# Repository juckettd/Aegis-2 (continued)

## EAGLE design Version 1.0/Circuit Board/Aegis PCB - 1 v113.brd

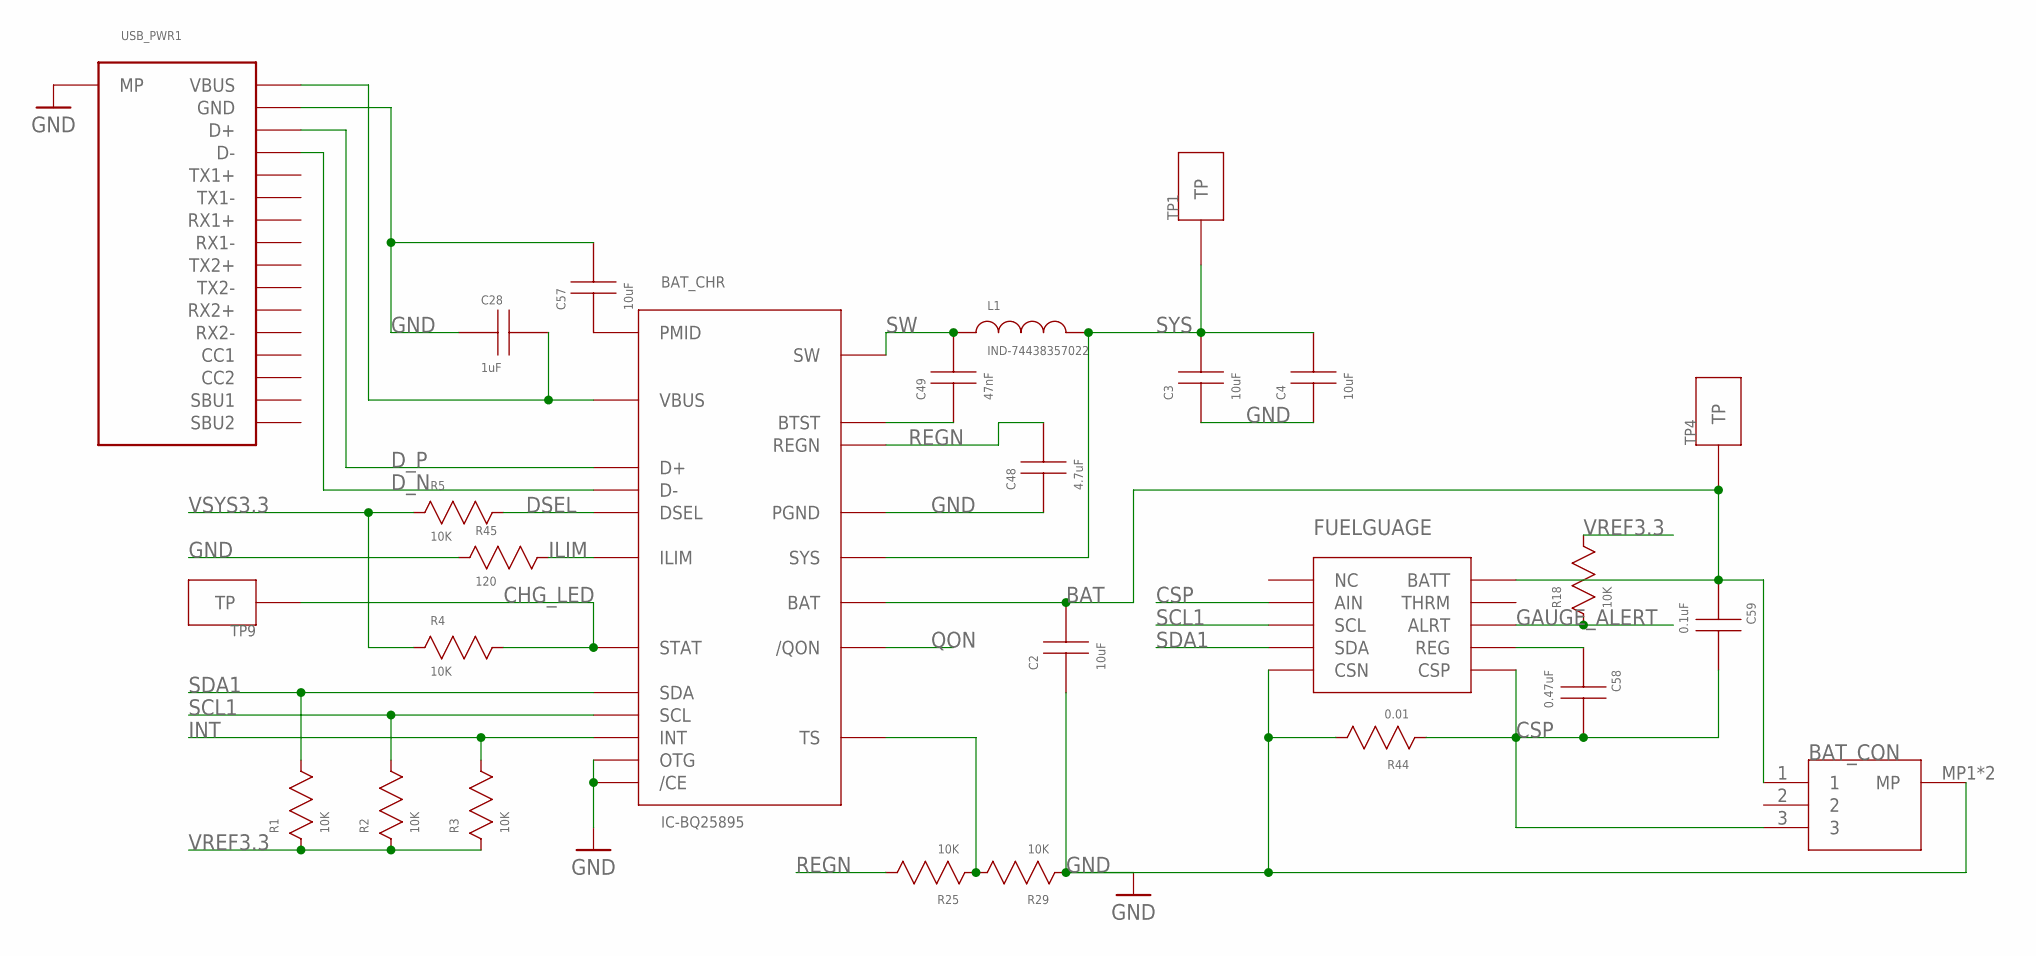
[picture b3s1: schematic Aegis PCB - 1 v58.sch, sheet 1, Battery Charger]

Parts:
BAT_CHR: IC-BQ25895
BAT_CON: CONN-AUH03; CONN_AUH03
C2, C3, C4, C57: 10uF; CAP-603
C28: 1uF; CAP-603
C48: 4.7uF; CAP-603
C49: 47nF; CAP-603
C58: 0.47uF; CAP-603
C59: 0.1uF; CAP-603
FUELGUAGE: IC-MAX17055
L1: IND-74438357022
R1, R2, R3, R4, R5, R18, R25, R29: 10K; RES-603
R44: 0.01; RES-603
R45: 120; RES-603
TP1, TP4, TP9: TESTPOINT
USB_PWR1: USBC-USB-C31-S-RA-CS1D-BK-T/R

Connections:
BAT: BAT_CHR.BAT1 (BAT), BAT_CHR.BAT2 (BAT), BAT_CON.1, C2.C, C59.A, FUELGUAGE.BATT, TP4.TP
CHG_LED: BAT_CHR.STAT, R4.C, TP9.TP; also elsewhere on the board
CSP: BAT_CON.3, C58.C, C59.C, FUELGUAGE.AIN, FUELGUAGE.CSP, FUELGUAGE.EP (CSP), R44.A
DSEL: BAT_CHR.DSEL, R5.C
D_N: BAT_CHR.D-, USB_PWR1.D-, USB_PWR1.D-_2 (D-)
D_P: BAT_CHR.D+, USB_PWR1.D+, USB_PWR1.D+_2 (D+)
GAUGE_ALERT: FUELGUAGE.ALRT, R18.A; also elsewhere on the board
ILIM: BAT_CHR.ILIM, R45.C
INT: BAT_CHR.INT, R3.C; also elsewhere on the board
unnamed: BAT_CHR.BTST, C49.A
unnamed: BAT_CHR.VBUS, C28.C, USB_PWR1.VBUS_1 (VBUS), USB_PWR1.VBUS_2 (VBUS), USB_PWR1.VBUS_3 (VBUS), USB_PWR1.VBUS_4 (VBUS)
unnamed: BAT_CHR.TS, R25.A, R29.C
unnamed: BAT_CHR.PMID, C57.A
unnamed: C58.A, FUELGUAGE.REG
QON: BAT_CHR./QON
REGN: BAT_CHR.REGN, C48.C, R25.C
SCL1: BAT_CHR.SCL, FUELGUAGE.SCL, R2.C; also elsewhere on the board
SDA1: BAT_CHR.SDA, FUELGUAGE.SDA, R1.C; also elsewhere on the board
SW: BAT_CHR.SW1 (SW), BAT_CHR.SW2 (SW), C49.C, L1.A
SYS: BAT_CHR.SYS1 (SYS), BAT_CHR.SYS2 (SYS), C3.C, C4.C, L1.C, TP1.TP; also elsewhere on the board
VREF3.3: R1.A, R2.A, R3.A, R18.C; also elsewhere on the board
VSYS3.3: R4.A, R5.A; also elsewhere on the board

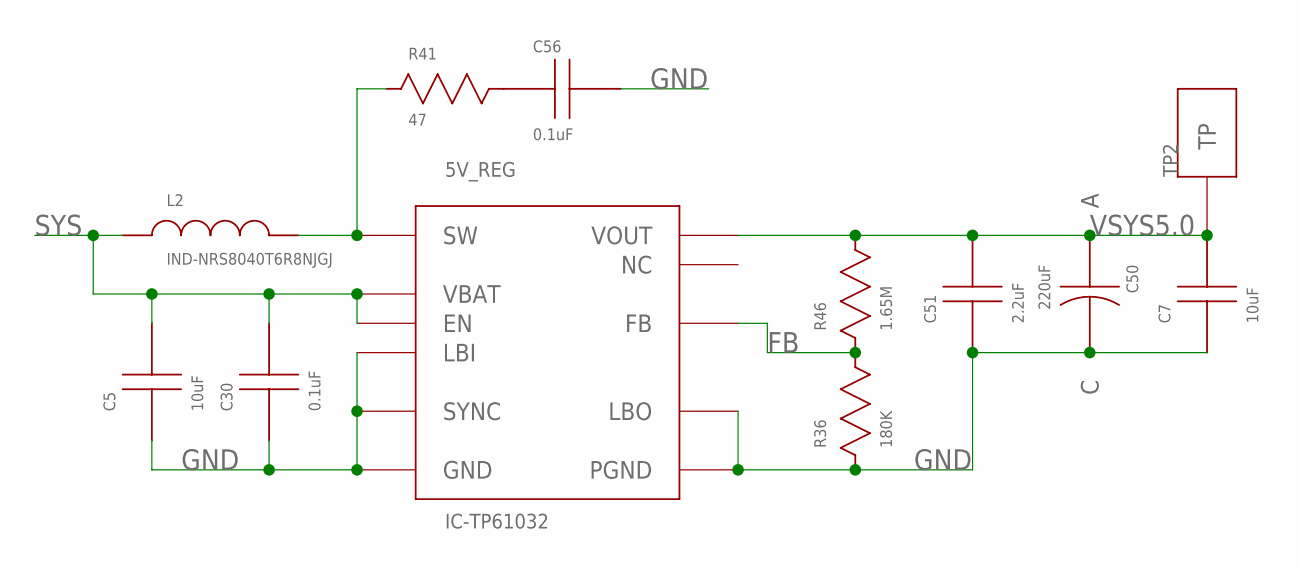
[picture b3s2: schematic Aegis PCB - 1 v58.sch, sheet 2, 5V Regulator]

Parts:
5V_REG: IC-TP61032; IC-TPS61032
C5, C7: 10uF; CAP-603
C30, C56: 0.1uF; CAP-603
C50: 220uF; CAP-TAN-1411
C51: 2.2uF; CAP-603
L2: IND-NRS8040T6R8NJGJ
R36: 180K; RES-603
R41: 47; RES-603
R46: 1.65M; RES-603
TP2: TESTPOINT

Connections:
FB: 5V_REG.FB, R36.C, R46.A
unnamed: C56.A, R41.C
SNUB: 5V_REG.SW1 (SW), 5V_REG.SW2 (SW), L2.C, R41.A
SYS: 5V_REG.EN, 5V_REG.VBAT, C5.C, C30.C, L2.A; also elsewhere on the board
VSYS5.0: 5V_REG.VOUT1 (VOUT), 5V_REG.VOUT2 (VOUT), 5V_REG.VOUT3 (VOUT), C7.C, C50.A, C51.C, R46.C, TP2.TP; also elsewhere on the board

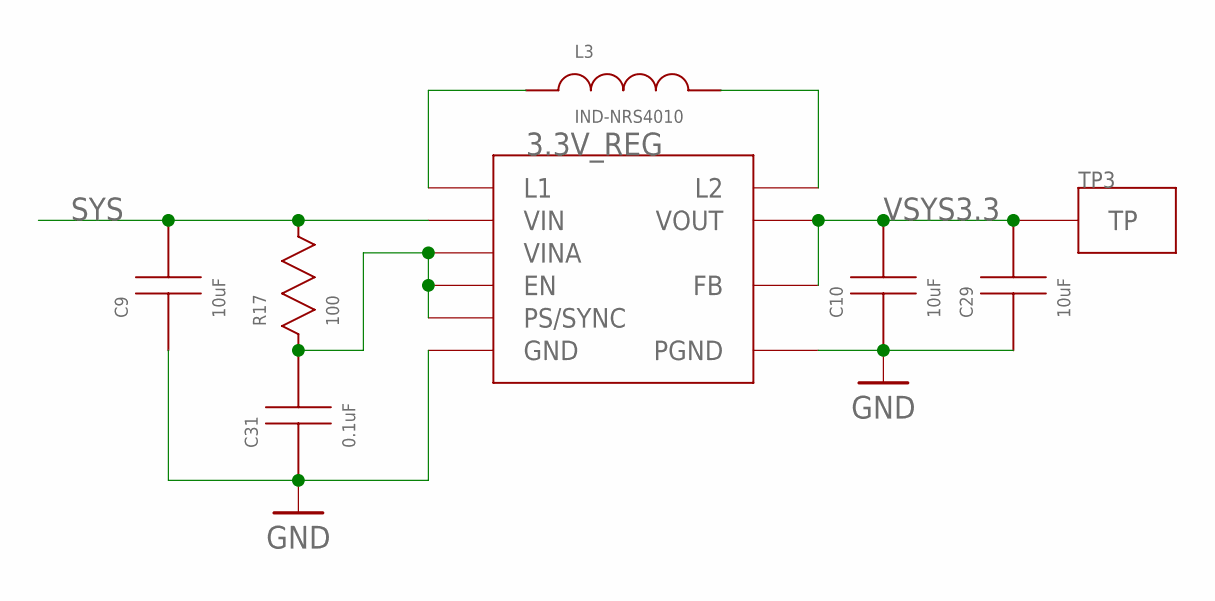
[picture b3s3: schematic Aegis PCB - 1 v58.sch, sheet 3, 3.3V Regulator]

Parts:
3.3V_REG: IC-TPS63001DRCR
C9, C10, C29: 10uF; CAP-603
C31: 0.1uF; CAP-603
L3: IND-NRS4010
R17: 100; RES-603
TP3: TESTPOINT

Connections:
unnamed: 3.3V_REG.EN, 3.3V_REG.PS/SYNC, 3.3V_REG.VINA, C31.C, R17.A
unnamed: 3.3V_REG.L1, L3.A
unnamed: 3.3V_REG.L2, L3.C
SYS: 3.3V_REG.VIN, C9.C, R17.C; also elsewhere on the board
VSYS3.3: 3.3V_REG.FB, 3.3V_REG.VOUT, C10.C, C29.C, TP3.TP; also elsewhere on the board

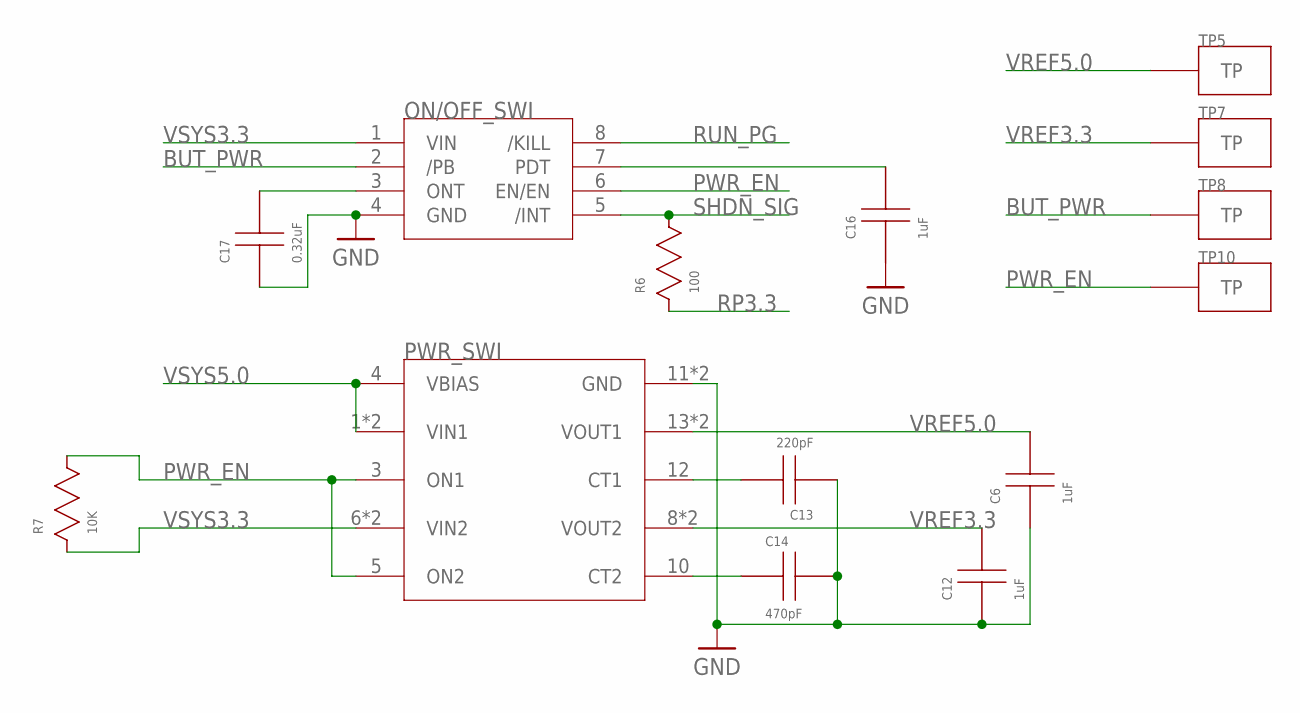
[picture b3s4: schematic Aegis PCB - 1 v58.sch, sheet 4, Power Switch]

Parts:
C6, C12, C16: 1uF; CAP-603
C13: 220pF; CAP-603
C14: 470pF; CAP-603
C17: 0.32uF; CAP-603
ON/OFF_SWI: IC-LTC2954
PWR_SWI: IC-TPS22976
R6: 100; RES-603
R7: 10K; RES-603
TP5, TP7, TP8, TP10: TESTPOINT

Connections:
BUT_PWR: ON/OFF_SWI.2 (/PB), TP8.TP; also elsewhere on the board
unnamed: C13.C, PWR_SWI.12 (CT1)
unnamed: C14.A, PWR_SWI.10 (CT2)
unnamed: C16.C, ON/OFF_SWI.7 (PDT)
unnamed: C17.C, ON/OFF_SWI.3 (ONT)
PWR_EN: ON/OFF_SWI.6 (EN/EN), PWR_SWI.3 (ON1), PWR_SWI.5 (ON2), R7.C, TP10.TP
RP3.3: R6.A; also elsewhere on the board
RUN_PG: ON/OFF_SWI.8 (/KILL); also elsewhere on the board
SHDN_SIG: ON/OFF_SWI.5 (/INT), R6.C; also elsewhere on the board
VREF3.3: C12.C, PWR_SWI.8 (VOUT2), PWR_SWI.9 (VOUT2), TP7.TP; also elsewhere on the board
VREF5.0: C6.C, PWR_SWI.13 (VOUT1), PWR_SWI.14 (VOUT1), TP5.TP; also elsewhere on the board
VSYS3.3: ON/OFF_SWI.1 (VIN), PWR_SWI.6 (VIN2), PWR_SWI.7 (VIN2), R7.A; also elsewhere on the board
VSYS5.0: PWR_SWI.1 (VIN1), PWR_SWI.2 (VIN1), PWR_SWI.4 (VBIAS); also elsewhere on the board

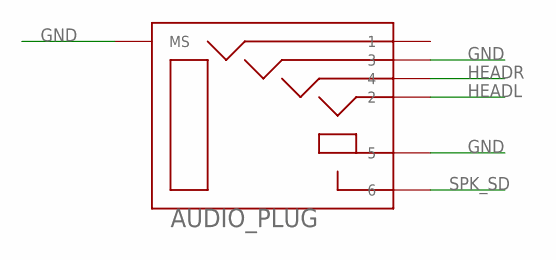
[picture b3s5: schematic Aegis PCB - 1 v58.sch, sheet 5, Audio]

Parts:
AUDIO_PLUG: AUDIOPLUG-ASJ-192-Y-TR

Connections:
HEADL: AUDIO_PLUG.2; also elsewhere on the board
HEADR: AUDIO_PLUG.4; also elsewhere on the board
SPK_SD: AUDIO_PLUG.6; also elsewhere on the board

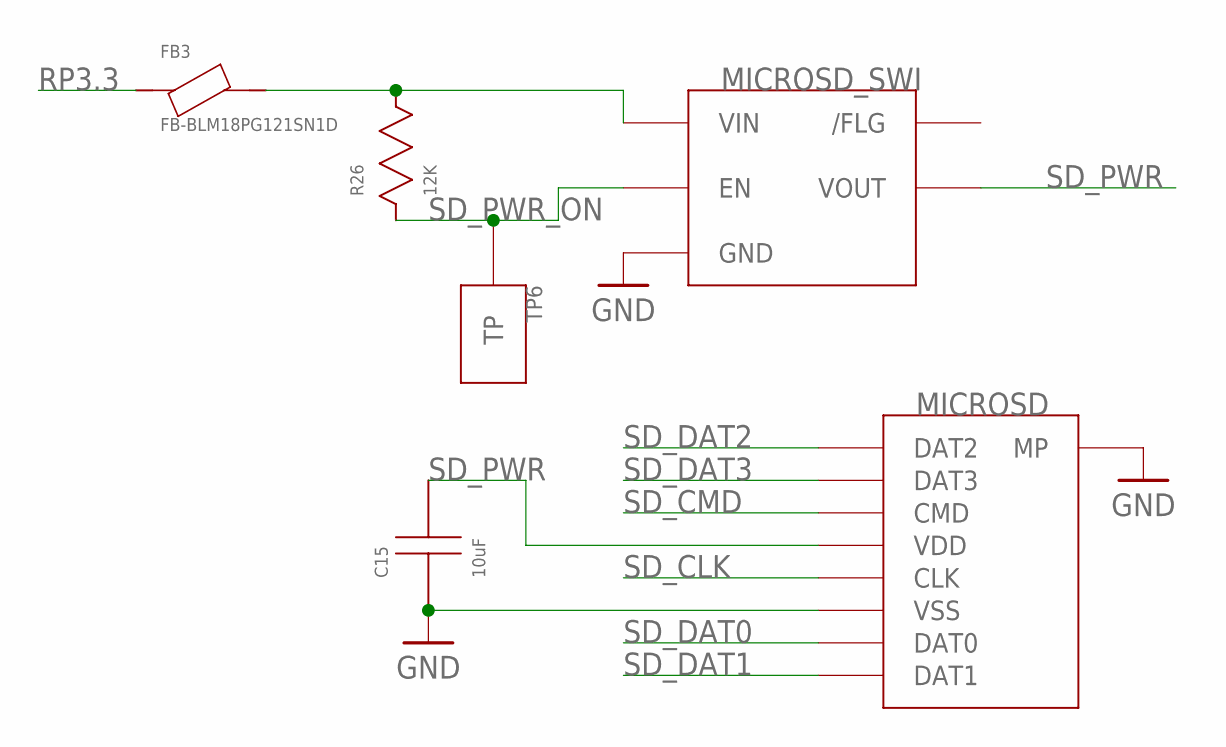
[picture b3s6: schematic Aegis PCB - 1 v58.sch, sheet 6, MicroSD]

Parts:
C15: 10uF; CAP-603
FB3: FB-BLM18PG121SN1D
MICROSD: MICROSD-5033981892_SD
MICROSD_SWI: IC-RT9742
R26: 12K; RES-603
TP6: TESTPOINT

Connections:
unnamed: FB3.C, MICROSD_SWI.VIN, R26.C
RP3.3: FB3.A; also elsewhere on the board
SD_CLK: MICROSD.CLK; also elsewhere on the board
SD_CMD: MICROSD.CMD; also elsewhere on the board
SD_DAT0: MICROSD.DAT0; also elsewhere on the board
SD_DAT1: MICROSD.DAT1; also elsewhere on the board
SD_DAT2: MICROSD.DAT2; also elsewhere on the board
SD_DAT3: MICROSD.DAT3; also elsewhere on the board
SD_PWR: C15.C, MICROSD.VDD, MICROSD_SWI.VOUT
SD_PWR_ON: MICROSD_SWI.EN, R26.A, TP6.TP; also elsewhere on the board

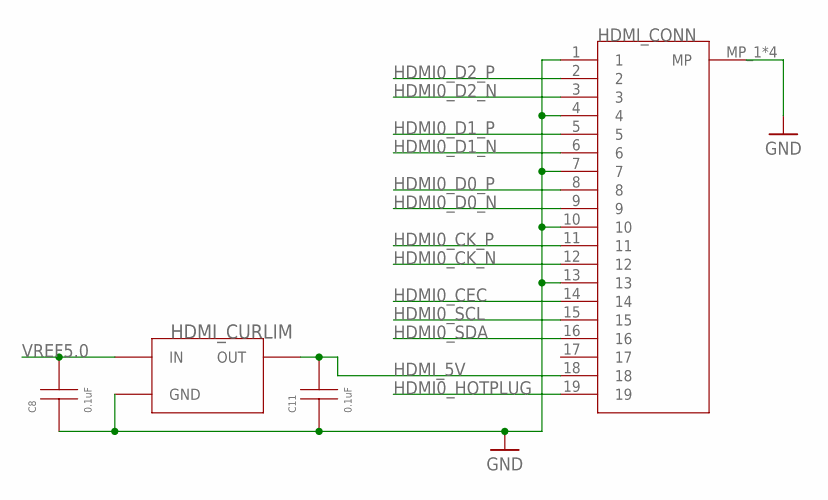
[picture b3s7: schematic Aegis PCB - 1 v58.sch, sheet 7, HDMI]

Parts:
C8, C11: 0.1uF; CAP-603
HDMI_CONN: HDMI-2001-1-2-21-00-BK
HDMI_CURLIM: CURLIM-AP2331

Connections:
HDMI0_CEC: HDMI_CONN.14; also elsewhere on the board
HDMI0_CK_N: HDMI_CONN.12; also elsewhere on the board
HDMI0_CK_P: HDMI_CONN.11; also elsewhere on the board
HDMI0_D0_N: HDMI_CONN.9; also elsewhere on the board
HDMI0_D0_P: HDMI_CONN.8; also elsewhere on the board
HDMI0_D1_N: HDMI_CONN.6; also elsewhere on the board
HDMI0_D1_P: HDMI_CONN.5; also elsewhere on the board
HDMI0_D2_N: HDMI_CONN.3; also elsewhere on the board
HDMI0_D2_P: HDMI_CONN.2; also elsewhere on the board
HDMI0_HOTPLUG: HDMI_CONN.19; also elsewhere on the board
HDMI0_SCL: HDMI_CONN.15; also elsewhere on the board
HDMI0_SDA: HDMI_CONN.16; also elsewhere on the board
HDMI_5V: C11.C, HDMI_CONN.18, HDMI_CURLIM.OUT
VREF5.0: C8.C, HDMI_CURLIM.IN; also elsewhere on the board

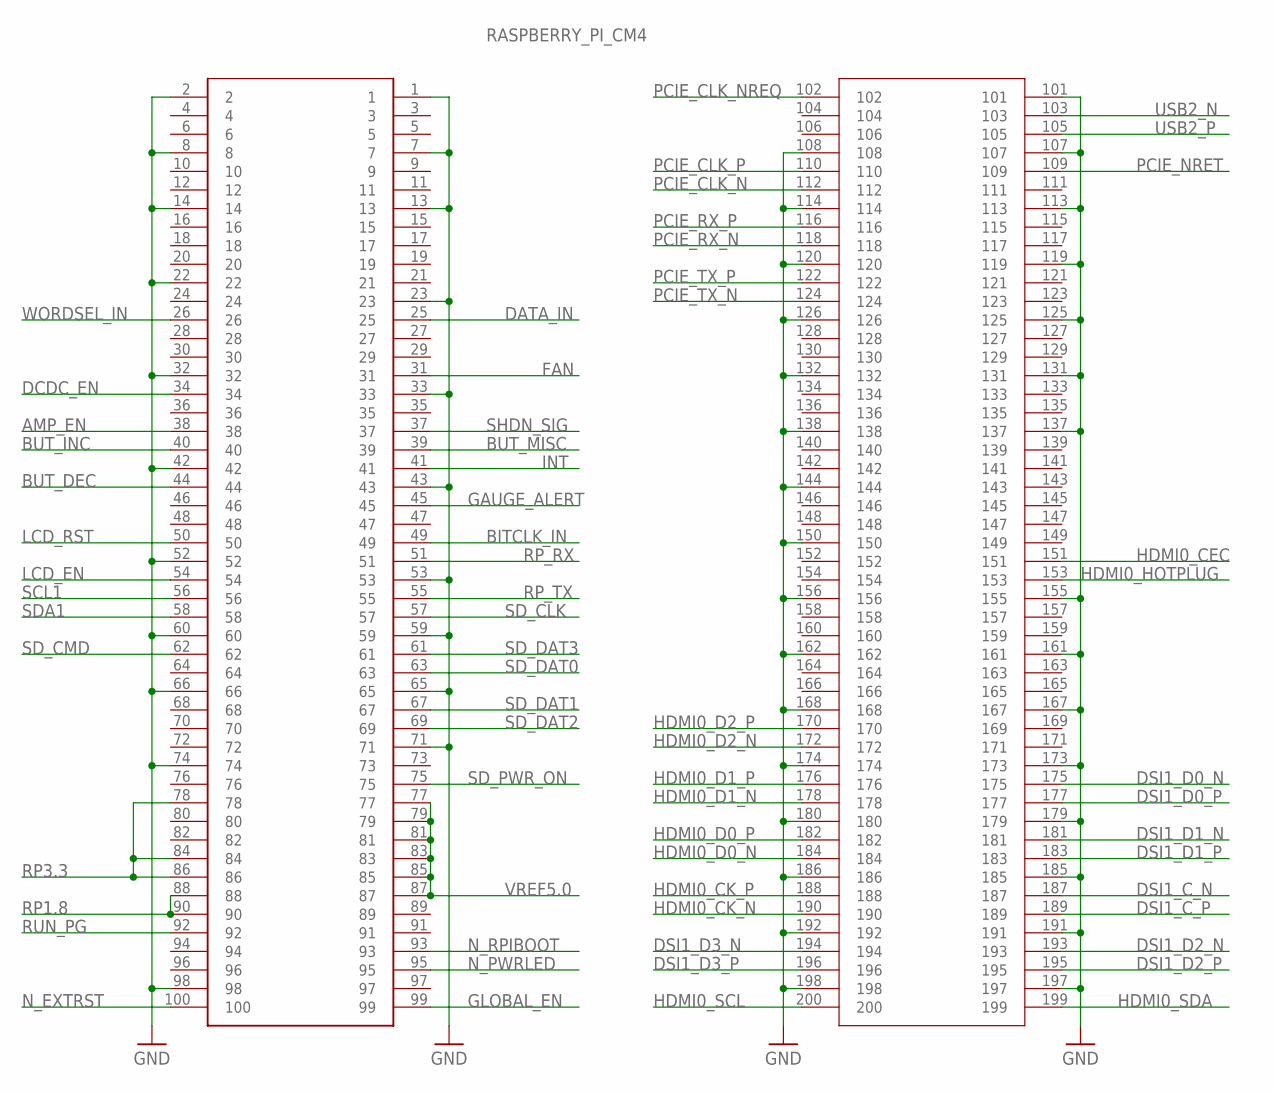
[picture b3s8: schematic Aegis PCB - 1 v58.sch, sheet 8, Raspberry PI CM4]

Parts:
RASPBERRY_PI_CM4: RP_CM4

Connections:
AMP_EN: RASPBERRY_PI_CM4.38; also elsewhere on the board
BITCLK_IN: RASPBERRY_PI_CM4.49; also elsewhere on the board
BUT_DEC: RASPBERRY_PI_CM4.44; also elsewhere on the board
BUT_INC: RASPBERRY_PI_CM4.40; also elsewhere on the board
BUT_MISC: RASPBERRY_PI_CM4.39; also elsewhere on the board
DATA_IN: RASPBERRY_PI_CM4.25; also elsewhere on the board
DCDC_EN: RASPBERRY_PI_CM4.34; also elsewhere on the board
DSI1_C_N: RASPBERRY_PI_CM4.187; also elsewhere on the board
DSI1_C_P: RASPBERRY_PI_CM4.189; also elsewhere on the board
DSI1_D0_N: RASPBERRY_PI_CM4.175; also elsewhere on the board
DSI1_D0_P: RASPBERRY_PI_CM4.177; also elsewhere on the board
DSI1_D1_N: RASPBERRY_PI_CM4.181; also elsewhere on the board
DSI1_D1_P: RASPBERRY_PI_CM4.183; also elsewhere on the board
DSI1_D2_N: RASPBERRY_PI_CM4.193; also elsewhere on the board
DSI1_D2_P: RASPBERRY_PI_CM4.195; also elsewhere on the board
DSI1_D3_N: RASPBERRY_PI_CM4.194; also elsewhere on the board
DSI1_D3_P: RASPBERRY_PI_CM4.196; also elsewhere on the board
FAN: RASPBERRY_PI_CM4.31; also elsewhere on the board
GAUGE_ALERT: RASPBERRY_PI_CM4.45; also elsewhere on the board
GLOBAL_EN: RASPBERRY_PI_CM4.99
HDMI0_CEC: RASPBERRY_PI_CM4.151; also elsewhere on the board
HDMI0_CK_N: RASPBERRY_PI_CM4.190; also elsewhere on the board
HDMI0_CK_P: RASPBERRY_PI_CM4.188; also elsewhere on the board
HDMI0_D0_N: RASPBERRY_PI_CM4.184; also elsewhere on the board
HDMI0_D0_P: RASPBERRY_PI_CM4.182; also elsewhere on the board
HDMI0_D1_N: RASPBERRY_PI_CM4.178; also elsewhere on the board
HDMI0_D1_P: RASPBERRY_PI_CM4.176; also elsewhere on the board
HDMI0_D2_N: RASPBERRY_PI_CM4.172; also elsewhere on the board
HDMI0_D2_P: RASPBERRY_PI_CM4.170; also elsewhere on the board
HDMI0_HOTPLUG: RASPBERRY_PI_CM4.153; also elsewhere on the board
HDMI0_SCL: RASPBERRY_PI_CM4.200; also elsewhere on the board
HDMI0_SDA: RASPBERRY_PI_CM4.199; also elsewhere on the board
INT: RASPBERRY_PI_CM4.41; also elsewhere on the board
LCD_EN: RASPBERRY_PI_CM4.54; also elsewhere on the board
LCD_RST: RASPBERRY_PI_CM4.50; also elsewhere on the board
N_EXTRST: RASPBERRY_PI_CM4.100; also elsewhere on the board
N_PWRLED: RASPBERRY_PI_CM4.95; also elsewhere on the board
N_RPIBOOT: RASPBERRY_PI_CM4.93
PCIE_CLK_N: RASPBERRY_PI_CM4.112
PCIE_CLK_NREQ: RASPBERRY_PI_CM4.102
PCIE_CLK_P: RASPBERRY_PI_CM4.110
PCIE_NRET: RASPBERRY_PI_CM4.109
PCIE_RX_N: RASPBERRY_PI_CM4.118
PCIE_RX_P: RASPBERRY_PI_CM4.116
PCIE_TX_N: RASPBERRY_PI_CM4.124
PCIE_TX_P: RASPBERRY_PI_CM4.122
RP1.8: RASPBERRY_PI_CM4.88, RASPBERRY_PI_CM4.90; also elsewhere on the board
RP3.3: RASPBERRY_PI_CM4.78, RASPBERRY_PI_CM4.84, RASPBERRY_PI_CM4.86; also elsewhere on the board
RUN_PG: RASPBERRY_PI_CM4.92; also elsewhere on the board
SCL1: RASPBERRY_PI_CM4.56; also elsewhere on the board
SDA1: RASPBERRY_PI_CM4.58; also elsewhere on the board
SD_CLK: RASPBERRY_PI_CM4.57; also elsewhere on the board
SD_CMD: RASPBERRY_PI_CM4.62; also elsewhere on the board
SD_DAT0: RASPBERRY_PI_CM4.63; also elsewhere on the board
SD_DAT1: RASPBERRY_PI_CM4.67; also elsewhere on the board
SD_DAT2: RASPBERRY_PI_CM4.69; also elsewhere on the board
SD_DAT3: RASPBERRY_PI_CM4.61; also elsewhere on the board
SD_PWR_ON: RASPBERRY_PI_CM4.75; also elsewhere on the board
SHDN_SIG: RASPBERRY_PI_CM4.37; also elsewhere on the board
USB2_N: RASPBERRY_PI_CM4.103; also elsewhere on the board
USB2_P: RASPBERRY_PI_CM4.105; also elsewhere on the board
VREF5.0: RASPBERRY_PI_CM4.77, RASPBERRY_PI_CM4.79, RASPBERRY_PI_CM4.81, RASPBERRY_PI_CM4.83, RASPBERRY_PI_CM4.85, RASPBERRY_PI_CM4.87; also elsewhere on the board
WORDSEL_IN: RASPBERRY_PI_CM4.26; also elsewhere on the board

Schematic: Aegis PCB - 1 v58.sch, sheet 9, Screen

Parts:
FPC_SCREEN: CONN-FH35C-31S-0.3SHW
SD1: SCHDIODE-SN74LVC1G17
TP11, TP12, TP13, TP15: TESTPOINT

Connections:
DCDC_EN: FPC_SCREEN.30, TP11.TP; also elsewhere on the board
DSI1_C_N: FPC_SCREEN.15; also elsewhere on the board
DSI1_C_P: FPC_SCREEN.16; also elsewhere on the board
DSI1_D0_N: FPC_SCREEN.12; also elsewhere on the board
DSI1_D0_P: FPC_SCREEN.13; also elsewhere on the board
DSI1_D1_N: FPC_SCREEN.18; also elsewhere on the board
DSI1_D1_P: FPC_SCREEN.19; also elsewhere on the board
DSI1_D2_N: FPC_SCREEN.21; also elsewhere on the board
DSI1_D2_P: FPC_SCREEN.22; also elsewhere on the board
DSI1_D3_N: FPC_SCREEN.9; also elsewhere on the board
DSI1_D3_P: FPC_SCREEN.10; also elsewhere on the board
LCD_EN: FPC_SCREEN.6, TP15.TP; also elsewhere on the board
LCD_RST: SD1.2 (A), TP13.TP; also elsewhere on the board
LCD_RST_ADJ: FPC_SCREEN.24, SD1.4 (Y), TP12.TP; also elsewhere on the board
RP1.8: FPC_SCREEN.31, SD1.5 (VCC); also elsewhere on the board
RP3.3: FPC_SCREEN.26, FPC_SCREEN.27; also elsewhere on the board
VREF3.3: FPC_SCREEN.1, FPC_SCREEN.2, FPC_SCREEN.3, FPC_SCREEN.4; also elsewhere on the board

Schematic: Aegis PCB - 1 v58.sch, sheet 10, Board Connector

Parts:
BOARD_CONN1: CONN-AXK5F30347YG

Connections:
AMP_EN: BOARD_CONN1.10; also elsewhere on the board
BITCLK_IN: BOARD_CONN1.2; also elsewhere on the board
BUT_DEC: BOARD_CONN1.5; also elsewhere on the board
BUT_INC: BOARD_CONN1.6; also elsewhere on the board
BUT_MISC: BOARD_CONN1.7; also elsewhere on the board
BUT_PWR: BOARD_CONN1.8; also elsewhere on the board
CHG_LED: BOARD_CONN1.9; also elsewhere on the board
DATA_IN: BOARD_CONN1.4; also elsewhere on the board
HEADL: BOARD_CONN1.12; also elsewhere on the board
HEADR: BOARD_CONN1.13; also elsewhere on the board
N_PWRLED: BOARD_CONN1.1; also elsewhere on the board
SPK_SD: BOARD_CONN1.11; also elsewhere on the board
TD_N: BOARD_CONN1.15; also elsewhere on the board
TD_P: BOARD_CONN1.14; also elsewhere on the board
VREF3.3: BOARD_CONN1.26, BOARD_CONN1.27, BOARD_CONN1.28, BOARD_CONN1.29; also elsewhere on the board
VSYS3.3: BOARD_CONN1.30; also elsewhere on the board
WORDSEL_IN: BOARD_CONN1.3; also elsewhere on the board

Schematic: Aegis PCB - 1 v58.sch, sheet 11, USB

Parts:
C1: 100uF; CAP-603
C19, C20, C21: 10uF; CAP-603
C43: 0.1uF; CAP-603
C52, C53: 27pF; CAP-603
CLK_24M: CLK-ECS-240
R27: 12K; RES-603
R28: 15K; RES-603
R30, R31, R32, R33: 36K; RES-603
TP14: TESTPOINT
USB_CURLIM: CURLIM-AP22653W6
USB_HUB: USBPORT-USB2514BT-I/M2
USB_POE: POE_PROT-TPD4EUSB30DQAR
USB_PWR2: USBC-USB-C31-S-RA-CS1D-BK-T/R

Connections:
D1_N: USB_HUB.3, USB_POE.D1-, USB_PWR2.D-, USB_PWR2.D-_2 (D-)
D1_P: USB_HUB.4, USB_POE.D1+, USB_PWR2.D+, USB_PWR2.D+_2 (D+)
unnamed: R32.A, USB_HUB.28
unnamed: R28.C, USB_CURLIM.ILIM
unnamed: R31.A, USB_HUB.22
unnamed: R30.A, USB_HUB.24
unnamed: C53.C, CLK_24M.OUT/IN, USB_HUB.32
unnamed: C52.C, CLK_24M.IN/OUT, USB_HUB.33
unnamed: R33.A, USB_HUB.25
unnamed: R27.A, USB_HUB.35
N_EXTRST: USB_HUB.26; also elsewhere on the board
N_OCS1: USB_CURLIM.NFAULT, USB_HUB.13, USB_HUB.17, USB_HUB.19, USB_HUB.21
PWR1: USB_CURLIM.EN, USB_HUB.12
TD_N: USB_HUB.1, USB_POE.D2-; also elsewhere on the board
TD_P: USB_HUB.2, USB_POE.D2+; also elsewhere on the board
USB2_N: USB_HUB.30; also elsewhere on the board
USB2_P: USB_HUB.31; also elsewhere on the board
VREF3.3: C19.C, C43.C, USB_HUB.5, USB_HUB.10, USB_HUB.15, USB_HUB.23, USB_HUB.27, USB_HUB.29, USB_HUB.36; also elsewhere on the board
VREF5.0: C20.C, USB_CURLIM.IN; also elsewhere on the board

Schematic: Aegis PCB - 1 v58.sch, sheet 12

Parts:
C44: 0.1uF; CAP-603
D3: DIODE-X3-WLB1608-2
FAN_CONN: CONN-282834-2
R19: 10K; RES-603
TP16: TESTPOINT
TR3: TRAN-DMG2302UKQ

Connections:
FAN: R19.C, TP16.TP, TR3.G; also elsewhere on the board
unnamed: D3.A, FAN_CONN.2, TR3.D
VREF3.3: C44.C, D3.C, FAN_CONN.1; also elsewhere on the board

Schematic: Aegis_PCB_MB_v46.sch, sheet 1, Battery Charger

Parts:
BAT_CHR: IC-BQ25895
BAT_CON: CONN-AUH03; CONN_AUH03
C2, C3, C4, C57: 10uF; CAP-603
C28: 1uF; CAP-603
C48: 4.7uF; CAP-603
C49: 47nF; CAP-603
C58: 0.47uF; CAP-603
C59: 0.1uF; CAP-603
FUELGUAGE: IC-MAX17055
L1: IND-74438357022
R1, R2, R3, R4, R5, R18, R25, R29: 10K; RES-603
R44: 0.01; RES-603
R45: 120; RES-603
TP1, TP9: TESTPOINT
USB_PWR1: USBC-USB-C31-S-RA-CS1D-BK-T/R

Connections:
BAT: BAT_CHR.BAT1 (BAT), BAT_CHR.BAT2 (BAT), BAT_CON.1, C2.C, C59.A, FUELGUAGE.BATT; also elsewhere on the board
CHG_LED: BAT_CHR.STAT, R4.C, TP9.TP; also elsewhere on the board
CSP: BAT_CON.3, C58.C, C59.C, FUELGUAGE.AIN, FUELGUAGE.CSP, FUELGUAGE.EP (CSP), R44.A
DSEL: BAT_CHR.DSEL, R5.C
D_N: BAT_CHR.D-, USB_PWR1.D-, USB_PWR1.D-_2 (D-)
D_P: BAT_CHR.D+, USB_PWR1.D+, USB_PWR1.D+_2 (D+)
GAUGE_ALERT: FUELGUAGE.ALRT, R18.A; also elsewhere on the board
ILIM: BAT_CHR.ILIM, R45.C
INT: BAT_CHR.INT, R3.C; also elsewhere on the board
unnamed: BAT_CHR.BTST, C49.A
unnamed: BAT_CHR.VBUS, C28.C, USB_PWR1.VBUS_1 (VBUS), USB_PWR1.VBUS_2 (VBUS), USB_PWR1.VBUS_3 (VBUS), USB_PWR1.VBUS_4 (VBUS)
unnamed: BAT_CHR.TS, R25.A, R29.C
unnamed: BAT_CHR.PMID, C57.A
unnamed: C58.A, FUELGUAGE.REG
QON: BAT_CHR./QON
REGN: BAT_CHR.REGN, C48.C, R25.C
SCL1: BAT_CHR.SCL, FUELGUAGE.SCL, R2.C; also elsewhere on the board
SDA1: BAT_CHR.SDA, FUELGUAGE.SDA, R1.C; also elsewhere on the board
SW: BAT_CHR.SW1 (SW), BAT_CHR.SW2 (SW), C49.C, L1.A
SYS: BAT_CHR.SYS1 (SYS), BAT_CHR.SYS2 (SYS), C3.C, C4.C, L1.C, TP1.TP; also elsewhere on the board
VREF3.3: R1.A, R2.A, R3.A, R18.C; also elsewhere on the board
VSYS3.3: R4.A, R5.A; also elsewhere on the board

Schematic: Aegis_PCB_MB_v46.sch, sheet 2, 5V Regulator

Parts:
5V_REG: IC-TP61032; IC-TPS61032
C5, C7: 10uF; CAP-603
C30, C56: 0.1uF; CAP-603
C50: 220uF; CAP-TAN-1411
C51: 2.2uF; CAP-603
L2: IND-NRS8040T6R8NJGJ
R36: 180K; RES-603
R41: 47; RES-603
R46: 1.65M; RES-603
TP2: TESTPOINT

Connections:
FB: 5V_REG.FB, R36.C, R46.A
unnamed: C56.A, R41.C
SNUB: 5V_REG.SW1 (SW), 5V_REG.SW2 (SW), L2.C, R41.A
SYS: 5V_REG.EN, 5V_REG.VBAT, C5.C, C30.C, L2.A; also elsewhere on the board
VSYS5.0: 5V_REG.VOUT1 (VOUT), 5V_REG.VOUT2 (VOUT), 5V_REG.VOUT3 (VOUT), C7.C, C50.A, C51.C, R46.C, TP2.TP; also elsewhere on the board

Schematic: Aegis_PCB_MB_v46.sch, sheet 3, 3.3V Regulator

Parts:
3.3V_REG: IC-TPS63001DRCR
C9, C10, C29: 10uF; CAP-603
C31: 0.1uF; CAP-603
L3: IND-NRS4010
R17: 100; RES-603
TP3: TESTPOINT

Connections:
unnamed: 3.3V_REG.EN, 3.3V_REG.PS/SYNC, 3.3V_REG.VINA, C31.C, R17.A
unnamed: 3.3V_REG.L1, L3.A
unnamed: 3.3V_REG.L2, L3.C
SYS: 3.3V_REG.VIN, C9.C, R17.C; also elsewhere on the board
VSYS3.3: 3.3V_REG.FB, 3.3V_REG.VOUT, C10.C, C29.C, TP3.TP; also elsewhere on the board

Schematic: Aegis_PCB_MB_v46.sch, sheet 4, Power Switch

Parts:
C6, C12, C16: 1uF; CAP-603
C13: 220pF; CAP-603
C14: 470pF; CAP-603
C17: 0.32uF; CAP-603
ON/OFF_SWI: IC-LTC2954
PWR_SWI: IC-TPS22976
R6: 100; RES-603
R7: 10K; RES-603

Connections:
BUT_PWR: ON/OFF_SWI.2 (/PB); also elsewhere on the board
unnamed: C13.C, PWR_SWI.12 (CT1)
unnamed: C14.A, PWR_SWI.10 (CT2)
unnamed: C16.C, ON/OFF_SWI.7 (PDT)
unnamed: C17.C, ON/OFF_SWI.3 (ONT)
PWR_EN: ON/OFF_SWI.6 (EN/EN), PWR_SWI.3 (ON1), PWR_SWI.5 (ON2), R7.C; also elsewhere on the board
RP3.3: R6.A; also elsewhere on the board
RUN_PG: ON/OFF_SWI.8 (/KILL); also elsewhere on the board
SHDN_SIG: ON/OFF_SWI.5 (/INT), R6.C; also elsewhere on the board
VREF3.3: C12.C, PWR_SWI.8 (VOUT2), PWR_SWI.9 (VOUT2); also elsewhere on the board
VREF5.0: C6.C, PWR_SWI.13 (VOUT1), PWR_SWI.14 (VOUT1); also elsewhere on the board
VSYS3.3: ON/OFF_SWI.1 (VIN), PWR_SWI.6 (VIN2), PWR_SWI.7 (VIN2), R7.A; also elsewhere on the board
VSYS5.0: PWR_SWI.1 (VIN1), PWR_SWI.2 (VIN1), PWR_SWI.4 (VBIAS); also elsewhere on the board

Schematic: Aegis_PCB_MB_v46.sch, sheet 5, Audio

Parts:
AUDIO_PLUG: AUDIOPLUG-ASJ-192-Y-TR

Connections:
HEADL: AUDIO_PLUG.2; also elsewhere on the board
HEADR: AUDIO_PLUG.4; also elsewhere on the board
SPK_SD: AUDIO_PLUG.6; also elsewhere on the board

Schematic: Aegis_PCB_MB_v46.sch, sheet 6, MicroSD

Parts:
C15: 10uF; CAP-603
FB3: FB-BLM18PG121SN1D
MICROSD: MICROSD-5033981892_SD
MICROSD_SWI: IC-RT9742
R26: 12K; RES-603
TP6: TESTPOINT

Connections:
unnamed: FB3.C, MICROSD_SWI.VIN, R26.C
RP3.3: FB3.A; also elsewhere on the board
SD_CLK: MICROSD.CLK; also elsewhere on the board
SD_CMD: MICROSD.CMD; also elsewhere on the board
SD_DAT0: MICROSD.DAT0; also elsewhere on the board
SD_DAT1: MICROSD.DAT1; also elsewhere on the board
SD_DAT2: MICROSD.DAT2; also elsewhere on the board
SD_DAT3: MICROSD.DAT3; also elsewhere on the board
SD_PWR: C15.C, MICROSD.VDD, MICROSD_SWI.VOUT
SD_PWR_ON: MICROSD_SWI.EN, R26.A, TP6.TP; also elsewhere on the board

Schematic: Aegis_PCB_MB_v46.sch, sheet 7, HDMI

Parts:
C8, C11: 0.1uF; CAP-603
HDMI_CONN: HDMI-2001-1-2-21-00-BK
HDMI_CURLIM: CURLIM-AP2331

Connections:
HDMI0_CEC: HDMI_CONN.14; also elsewhere on the board
HDMI0_CK_N: HDMI_CONN.12; also elsewhere on the board
HDMI0_CK_P: HDMI_CONN.11; also elsewhere on the board
HDMI0_D0_N: HDMI_CONN.9; also elsewhere on the board
HDMI0_D0_P: HDMI_CONN.8; also elsewhere on the board
HDMI0_D1_N: HDMI_CONN.6; also elsewhere on the board
HDMI0_D1_P: HDMI_CONN.5; also elsewhere on the board
HDMI0_D2_N: HDMI_CONN.3; also elsewhere on the board
HDMI0_D2_P: HDMI_CONN.2; also elsewhere on the board
HDMI0_HOTPLUG: HDMI_CONN.19; also elsewhere on the board
HDMI0_SCL: HDMI_CONN.15; also elsewhere on the board
HDMI0_SDA: HDMI_CONN.16; also elsewhere on the board
HDMI_5V: C11.C, HDMI_CONN.18, HDMI_CURLIM.OUT
VREF5.0: C8.C, HDMI_CURLIM.IN; also elsewhere on the board

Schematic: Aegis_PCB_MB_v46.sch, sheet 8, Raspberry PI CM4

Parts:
U$9: RP_CM4

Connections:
unnamed: U$9.1, U$9.2, U$9.7, U$9.8, U$9.13, U$9.14, U$9.22, U$9.23, U$9.32, U$9.33, U$9.42, U$9.43, U$9.52, U$9.53, U$9.59, U$9.60, U$9.65, U$9.66, U$9.71, U$9.74, U$9.98, U$9.101, U$9.107, U$9.108, U$9.113, U$9.114, U$9.119, U$9.120, U$9.125, U$9.126, U$9.131, U$9.132, U$9.137, U$9.138, U$9.144, U$9.150, U$9.155, U$9.156, U$9.161, U$9.162, U$9.167, U$9.168, U$9.173, U$9.174, U$9.179, U$9.180, U$9.185, U$9.186, U$9.191, U$9.192, U$9.197, U$9.198
unnamed: U$9.77, U$9.79, U$9.81, U$9.83, U$9.85, U$9.87
unnamed: U$9.78, U$9.84, U$9.86
unnamed: U$9.88, U$9.90

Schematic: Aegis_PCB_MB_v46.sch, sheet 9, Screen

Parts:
FPC_SCREEN: CONN-FH35C-31S-0.3SHW
R8, R9, R10: 10K; RES-603
SD1: SCHDIODE-SN74LVC1G17

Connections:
DCDC_EN: FPC_SCREEN.30, R8.A; also elsewhere on the board
DSI1_C_N: FPC_SCREEN.15; also elsewhere on the board
DSI1_C_P: FPC_SCREEN.16; also elsewhere on the board
DSI1_D0_N: FPC_SCREEN.12; also elsewhere on the board
DSI1_D0_P: FPC_SCREEN.13; also elsewhere on the board
DSI1_D1_N: FPC_SCREEN.18; also elsewhere on the board
DSI1_D1_P: FPC_SCREEN.19; also elsewhere on the board
DSI1_D2_N: FPC_SCREEN.21; also elsewhere on the board
DSI1_D2_P: FPC_SCREEN.22; also elsewhere on the board
DSI1_D3_N: FPC_SCREEN.9; also elsewhere on the board
DSI1_D3_P: FPC_SCREEN.10; also elsewhere on the board
LCD_EN: FPC_SCREEN.6, R10.A; also elsewhere on the board
LCD_RST: SD1.2 (A); also elsewhere on the board
LCD_RST_ADJ: FPC_SCREEN.24, R9.A, SD1.4 (Y); also elsewhere on the board
RP1.8: FPC_SCREEN.31, SD1.5 (VCC); also elsewhere on the board
RP3.3: FPC_SCREEN.26, FPC_SCREEN.27; also elsewhere on the board
VREF3.3: FPC_SCREEN.1, FPC_SCREEN.2, FPC_SCREEN.3, FPC_SCREEN.4; also elsewhere on the board

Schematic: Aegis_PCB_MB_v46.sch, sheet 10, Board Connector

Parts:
BOARD_CONN1: CONN-AXK5F30347YG

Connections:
AMP_EN: BOARD_CONN1.10; also elsewhere on the board
BITCLK_IN: BOARD_CONN1.2; also elsewhere on the board
BUT_DEC: BOARD_CONN1.5; also elsewhere on the board
BUT_INC: BOARD_CONN1.6; also elsewhere on the board
BUT_MISC: BOARD_CONN1.7; also elsewhere on the board
BUT_PWR: BOARD_CONN1.8; also elsewhere on the board
CHG_LED: BOARD_CONN1.9; also elsewhere on the board
DATA_IN: BOARD_CONN1.4; also elsewhere on the board
HEADL: BOARD_CONN1.12; also elsewhere on the board
HEADR: BOARD_CONN1.13; also elsewhere on the board
N_PWRLED: BOARD_CONN1.1; also elsewhere on the board
SPK_SD: BOARD_CONN1.11; also elsewhere on the board
TD_N: BOARD_CONN1.15; also elsewhere on the board
TD_P: BOARD_CONN1.14; also elsewhere on the board
VREF3.3: BOARD_CONN1.26, BOARD_CONN1.27, BOARD_CONN1.28, BOARD_CONN1.29; also elsewhere on the board
VSYS3.3: BOARD_CONN1.30; also elsewhere on the board
WORDSEL_IN: BOARD_CONN1.3; also elsewhere on the board

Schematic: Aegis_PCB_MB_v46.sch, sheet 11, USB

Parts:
C1: 100uF; CAP-603
C19, C20, C21: 10uF; CAP-603
C43: 0.1uF; CAP-603
C52, C53: 27pF; CAP-603
CLK_24M: CLK-ECS-240
R27: 12K; RES-603
R28: 15K; RES-603
R30, R31, R32, R33: 36K; RES-603
TP14: TESTPOINT
USB_CURLIM: CURLIM-AP22653W6
USB_HUB: USBPORT-USB2514BT-I/M2
USB_POE: POE_PROT-TPD4EUSB30DQAR
USB_PWR2: USBC-USB-C31-S-RA-CS1D-BK-T/R

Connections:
D1_N: USB_HUB.3, USB_POE.D1-, USB_PWR2.D-, USB_PWR2.D-_2 (D-)
D1_P: USB_HUB.4, USB_POE.D1+, USB_PWR2.D+, USB_PWR2.D+_2 (D+)
unnamed: R32.A, USB_HUB.28
unnamed: R28.C, USB_CURLIM.ILIM
unnamed: R31.A, USB_HUB.22
unnamed: R30.A, USB_HUB.24
unnamed: C53.C, CLK_24M.OUT/IN, USB_HUB.32
unnamed: C52.C, CLK_24M.IN/OUT, USB_HUB.33
unnamed: R33.A, USB_HUB.25
unnamed: R27.A, USB_HUB.35
N_EXTRST: USB_HUB.26; also elsewhere on the board
N_OCS1: USB_CURLIM.NFAULT, USB_HUB.13, USB_HUB.17, USB_HUB.19, USB_HUB.21
PWR1: USB_CURLIM.EN, USB_HUB.12
TD_N: USB_HUB.1, USB_POE.D2-; also elsewhere on the board
TD_P: USB_HUB.2, USB_POE.D2+; also elsewhere on the board
USB2_N: USB_HUB.30; also elsewhere on the board
USB2_P: USB_HUB.31; also elsewhere on the board
VREF3.3: C19.C, C43.C, USB_HUB.5, USB_HUB.10, USB_HUB.15, USB_HUB.23, USB_HUB.27, USB_HUB.29, USB_HUB.36; also elsewhere on the board
VREF5.0: C20.C, USB_CURLIM.IN; also elsewhere on the board

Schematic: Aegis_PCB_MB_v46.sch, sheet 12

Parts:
C44: 0.1uF; CAP-603
D3: DIODE-X3-WLB1608-2
FAN_CONN: CONN-282834-2
R19: 10K; RES-603
TP16: TESTPOINT
TR3: TRAN-DMG2302UKQ

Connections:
FAN: R19.C, TP16.TP, TR3.G; also elsewhere on the board
unnamed: D3.A, FAN_CONN.2, TR3.D
VREF3.3: C44.C, D3.C, FAN_CONN.1; also elsewhere on the board

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
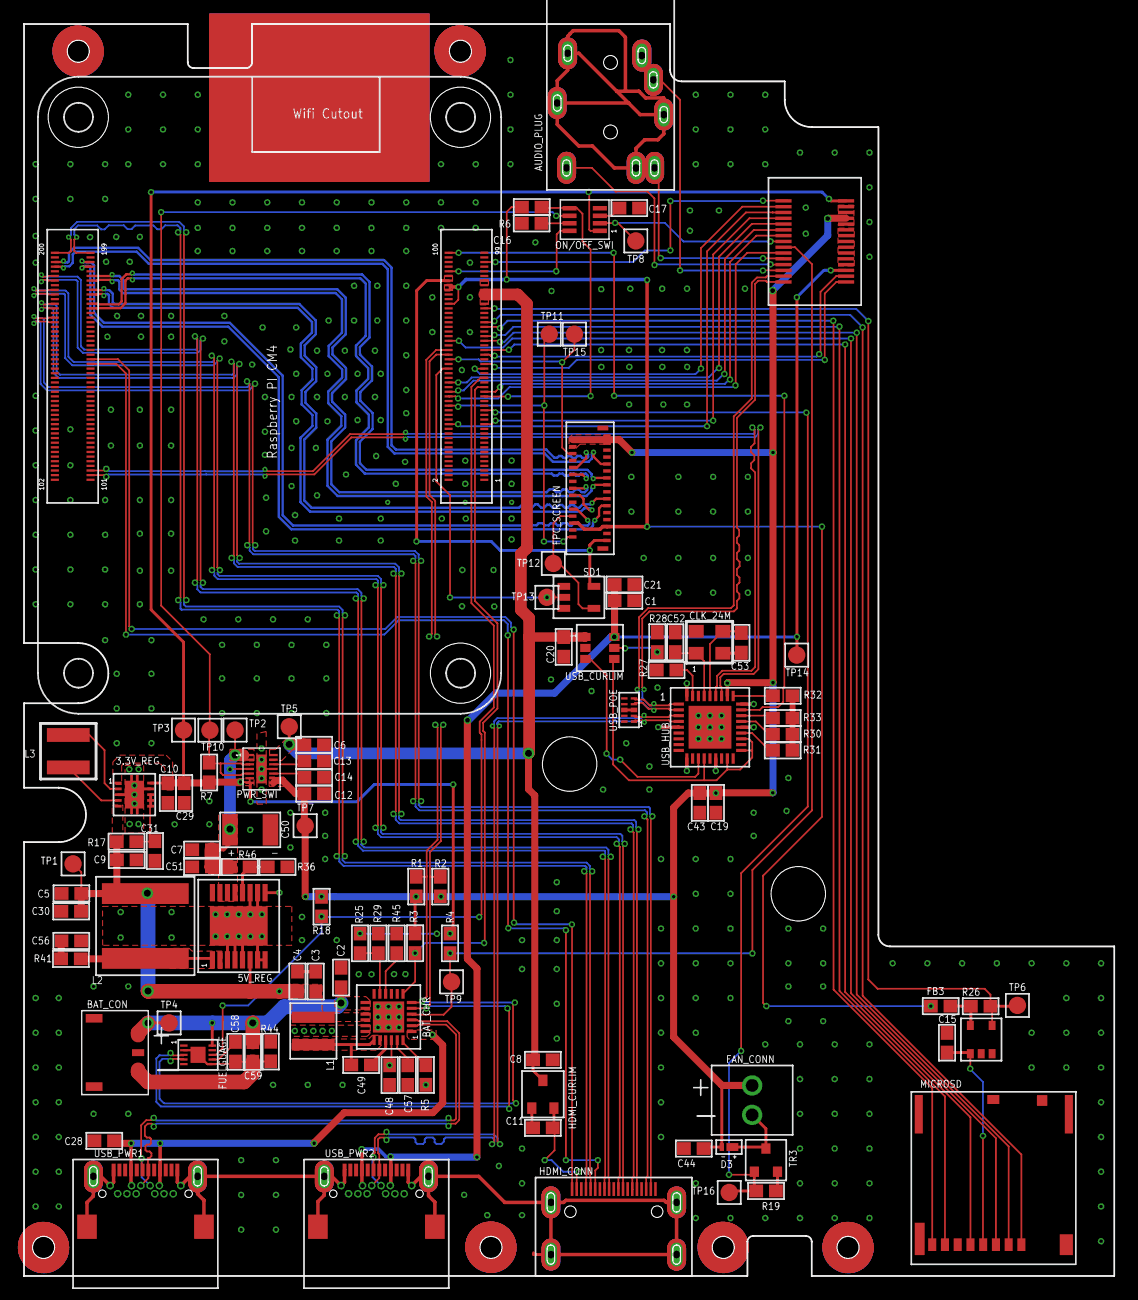
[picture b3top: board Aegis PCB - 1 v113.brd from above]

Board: 4 copper layers, 94.1 x 108.1 mm, 105 parts (0 on the bottom side), 109 nets.
